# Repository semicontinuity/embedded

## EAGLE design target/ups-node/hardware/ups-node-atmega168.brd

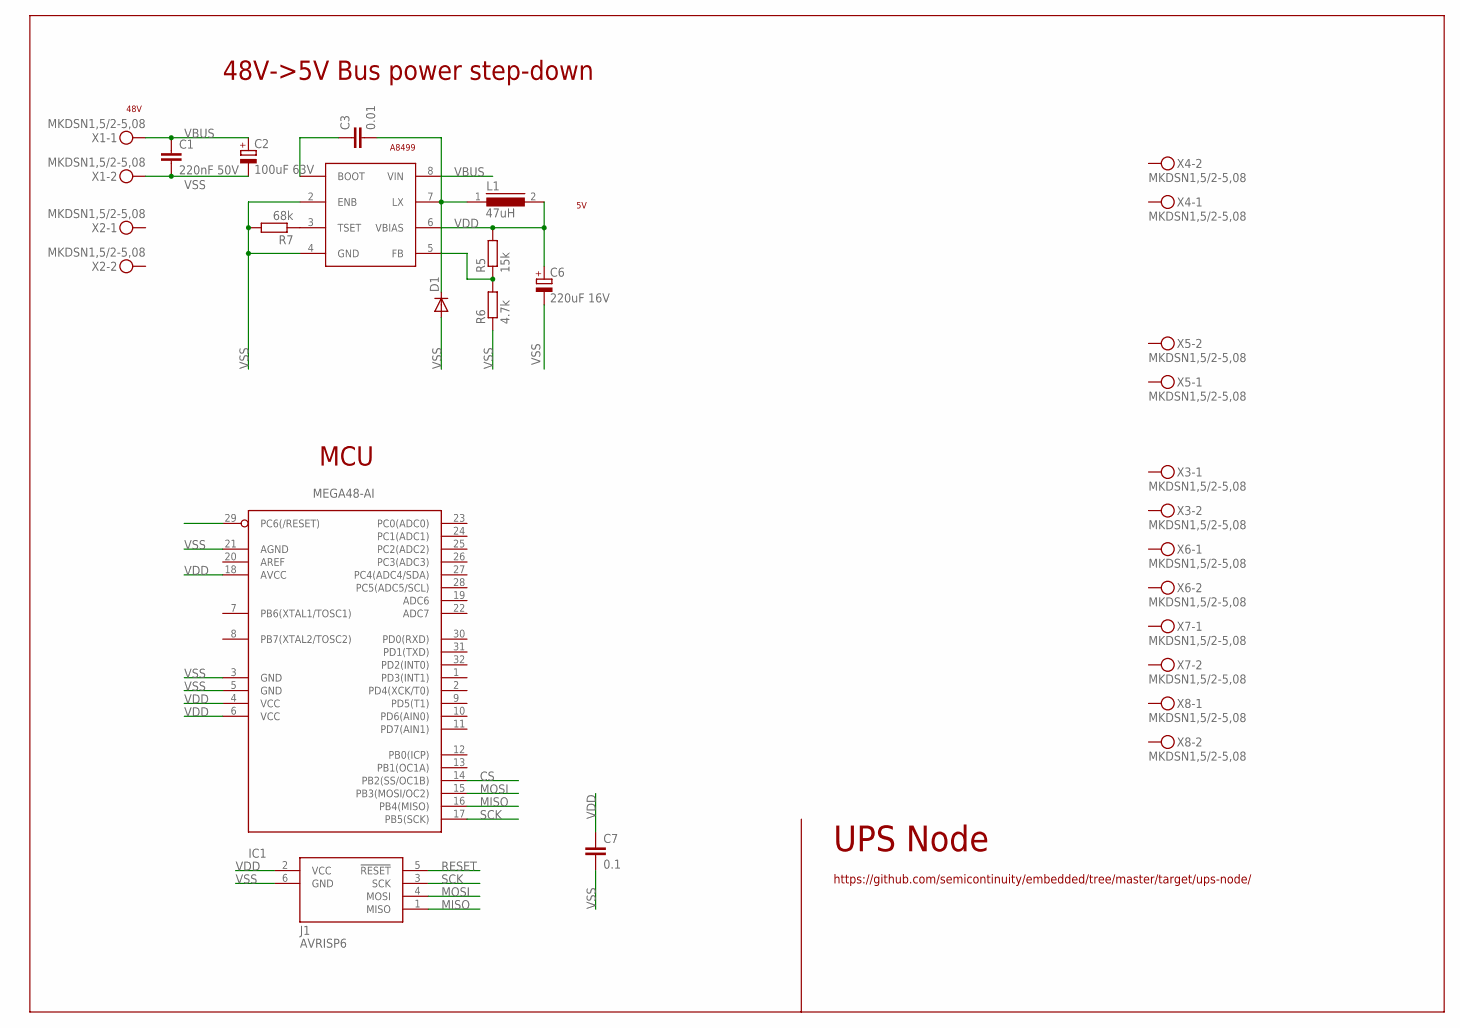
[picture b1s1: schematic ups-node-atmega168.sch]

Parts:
C1: 220nF 50V; C0805
C2: 100uF 63V; 153CLV-1010
C3: 0.01; C0805
C6: 220uF 16V; 153CLV-0605
C7: 0.1; C0805
D1: DIODE-SMB; SMB
IC1: MEGA48-AI; TQFP32-08
J1: AVRISP6; CON6P2R
L1: 47uH; DR127
R5: 15k; R0805
R6: 4.7k; R0805
R7: 68k; R0805
U$1: A8499; SO08
X1, X2, X3, X4, X5, X6, X7, X8: MKDSN1,5/2-5,08

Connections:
BOOT: C3.1, U$1.1 (BOOT)
CS: IC1.14 (PB2(SS/OC1B))
LX: C3.2, D1.C, L1.1, U$1.7 (LX)
MISO: IC1.16 (PB4(MISO)), J1.1 (MISO)
MOSI: IC1.15 (PB3(MOSI/OC2)), J1.4 (MOSI)
unnamed: R5.1, R6.2, U$1.5 (FB)
unnamed: R7.1, U$1.3 (TSET)
RESET: IC1.29 (PC6(/RESET)), J1.5 (!RESET)
SCK: IC1.17 (PB5(SCK)), J1.3 (SCK)
VBUS: C1.1, C2.+, U$1.8 (VIN), X1.1
VDD: C6.+, C7.1, IC1.4 (VCC), IC1.6 (VCC), IC1.18 (AVCC), J1.2 (VCC), L1.2, R5.2, U$1.6 (VBIAS)
VSS: C1.2, C2.-, C6.-, C7.2, D1.A, IC1.3 (GND), IC1.5 (GND), IC1.21 (AGND), J1.6 (GND), R6.1, R7.2, U$1.2 (ENB), U$1.4 (GND), X1.2

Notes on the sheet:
UPS Node
https://github.com/semicontinuity/embedded/tree/master/target/ups-node/
48V->5V Bus power step-down
MCU
A8499
48V

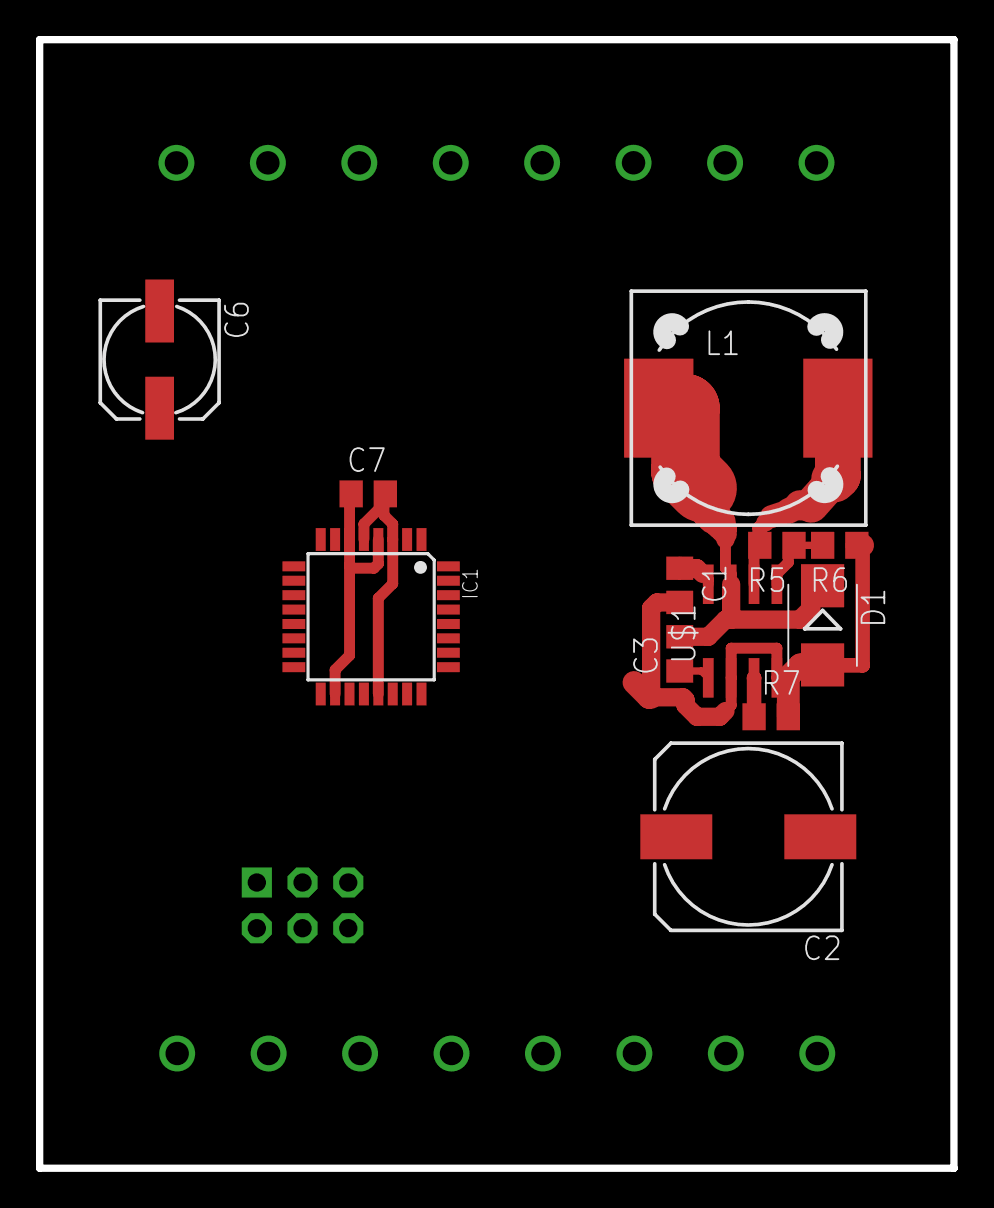
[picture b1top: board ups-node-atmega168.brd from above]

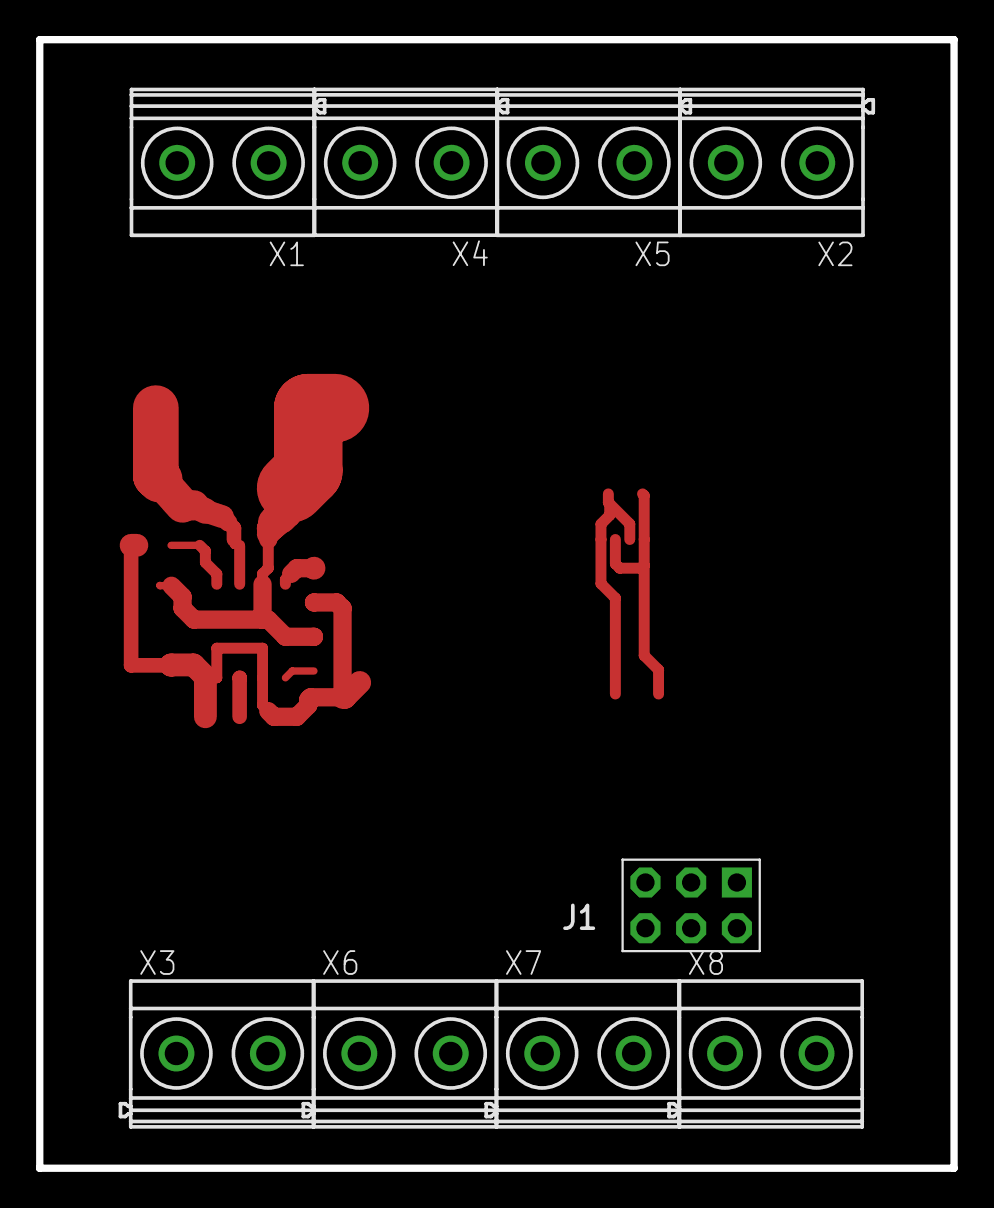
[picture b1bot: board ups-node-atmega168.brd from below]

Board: 2 copper layers, 50.8 x 62.7 mm, 21 parts (9 on the bottom side), 11 nets.

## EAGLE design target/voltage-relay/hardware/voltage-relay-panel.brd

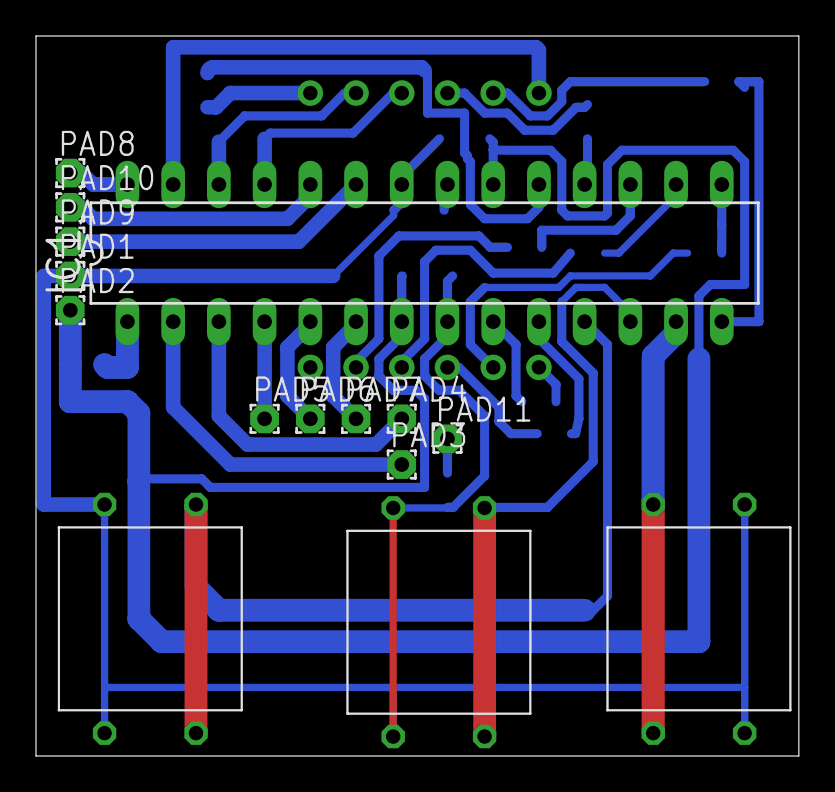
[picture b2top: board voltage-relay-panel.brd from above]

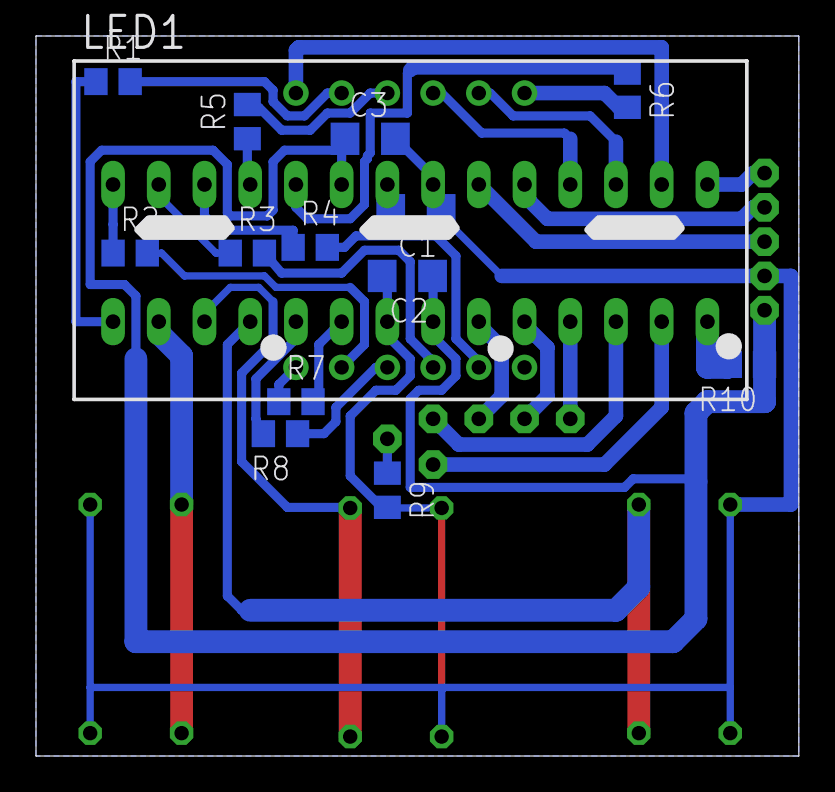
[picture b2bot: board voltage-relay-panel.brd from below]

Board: 2 copper layers, 42.4 x 40.0 mm, 29 parts (14 on the bottom side), 35 nets.

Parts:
C1, C2, C3: 0.1; C1206
IC1: MEGA8-P; DIL28-3
LED1: BA56-12YWA; BX56-12
PAD1, PAD2, PAD3, PAD4, PAD5, PAD6, PAD7, PAD8, PAD9, PAD10, PAD11: 1,6/0,8
R1, R2, R3, R4, R5, R6, R7, R8, R9: 470; R0805
R10: 10K; R0805
U$1, U$2, U$3: TL1105; LARGE

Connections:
B_MINUS: IC1.13, U$1.P$1, U$1.P$2
B_MODE: IC1.11, U$3.P$1, U$3.P$2
B_PLUS: IC1.12, U$2.P$1, U$2.P$2
DISP_A: LED1.11, R1.2
DISP_B: LED1.7, R6.2
DISP_C: LED1.4, R3.2
DISP_CA1: IC1.27, LED1.12
DISP_CA2: IC1.25, LED1.9
DISP_CA3: IC1.26, LED1.8
DISP_D: LED1.2, R2.2
DISP_DP: LED1.3, R8.1
DISP_E: LED1.1, R7.1
DISP_F: LED1.10, R5.2
DISP_G: LED1.5, R4.2
GND: C1.1, C2.2, C3.2, IC1.8, IC1.22, PAD1.1, R9.2, U$1.P$3, U$1.P$4, U$2.P$3, U$2.P$4, U$3.P$3, U$3.P$4
GPIO0: IC1.4, PAD5.1
GPIO1: IC1.5, PAD6.1
GPIO2: IC1.6, PAD7.1
GPIO3: IC1.23, PAD9.1
GPIO4: IC1.24, PAD10.1
GPIO5: IC1.28, PAD8.1
LED_G: IC1.3, PAD4.1
LED_R: IC1.2, PAD3.1
unnamed: IC1.1, R10.2
unnamed: PAD11.1, R9.1
unnamed: IC1.14, R1.1
unnamed: IC1.15, R2.1
unnamed: IC1.16, R3.1
unnamed: IC1.17, R4.1
unnamed: IC1.18, R5.1
unnamed: IC1.19, R6.1
unnamed: IC1.9, R7.2
unnamed: IC1.10, R8.2
unnamed: C1.2, IC1.21
VCC: C2.1, C3.1, IC1.7, IC1.20, PAD2.1, R10.1

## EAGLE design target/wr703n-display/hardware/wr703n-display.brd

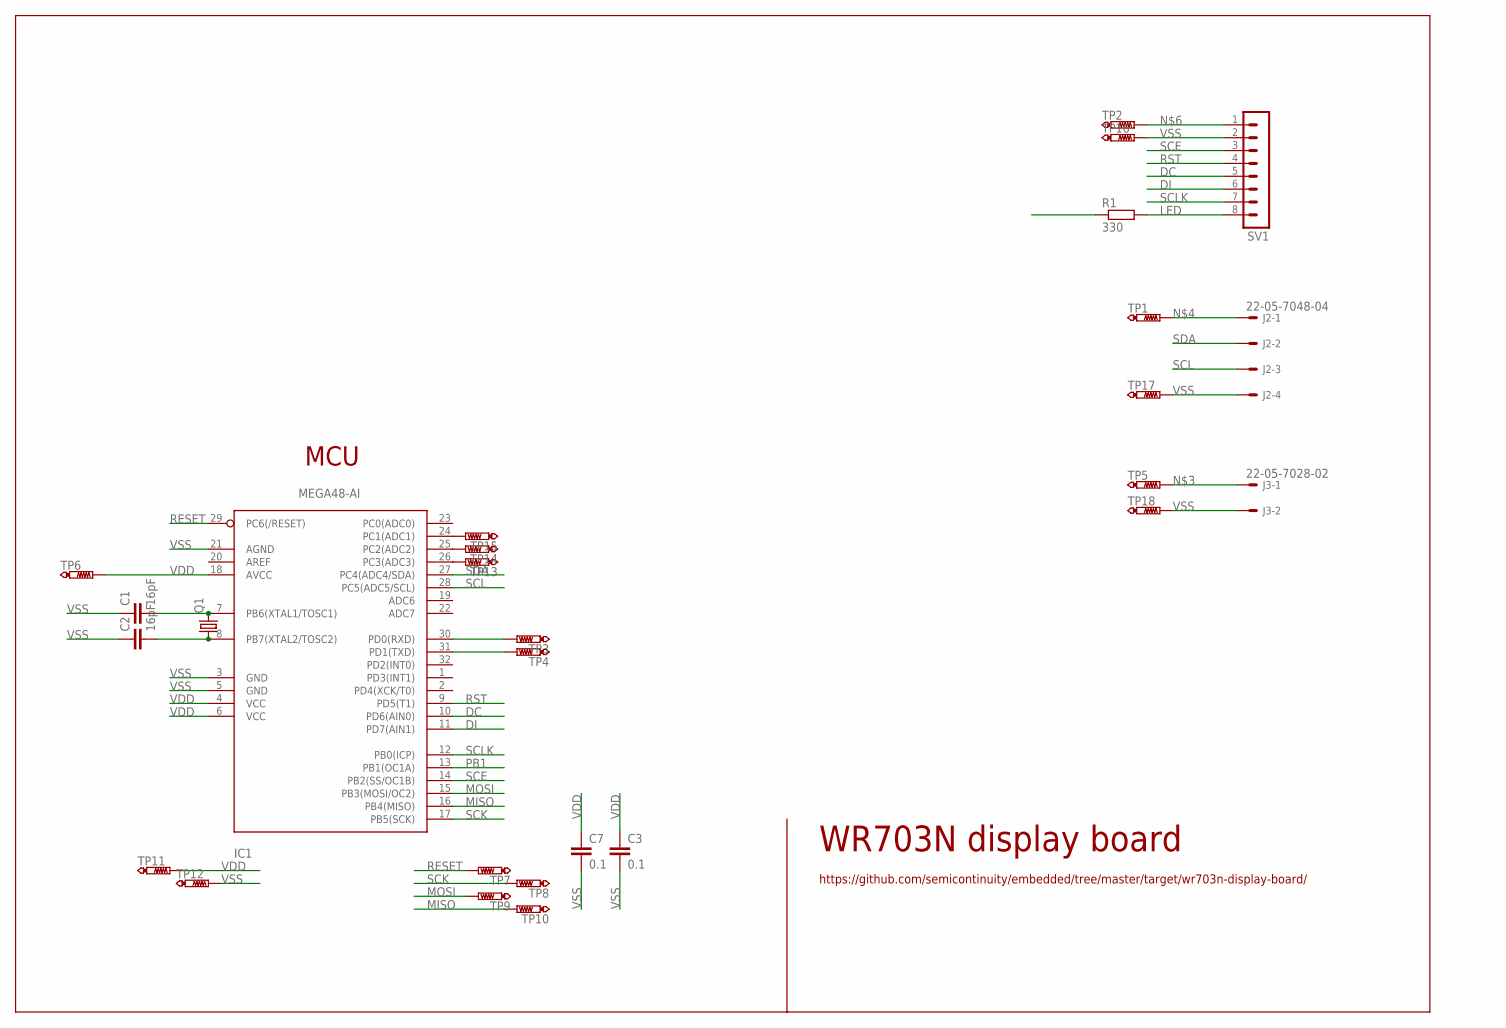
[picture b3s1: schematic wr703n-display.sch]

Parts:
C1, C2: 16pF; C0805
C3, C7: 0.1; C0805
IC1: MEGA48-AI; TQFP32-08
J2: 22-05-7048-04; 7395-04
J3: 22-05-7028-02; 7395-02
Q1: CRYSTALHC49S; HC49/S
R1: 330; R0805
SV1: MA08-1
TP1, TP2, TP3, TP4, TP5, TP6, TP16, TP17, TP18: PTR1B2,54; B2,54
TP7, TP8, TP9, TP10, TP11, TP12, TP13, TP14, TP15: PTR1TP17R; TP17R

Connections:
DC: IC1.10 (PD6(AIN0)), SV1.5
DI: IC1.11 (PD7(AIN1)), SV1.6
LED: R1.2, SV1.8
MISO: IC1.16 (PB4(MISO)), TP10.TP
MOSI: IC1.15 (PB3(MOSI/OC2)), TP9.TP
unnamed: C1.2, IC1.7 (PB6(XTAL1/TOSC1)), Q1.2
unnamed: C2.2, IC1.8 (PB7(XTAL2/TOSC2)), Q1.1
unnamed: J3.1, TP5.TP
unnamed: J2.1, TP1.TP
unnamed: IC1.31 (PD1(TXD)), TP4.TP
unnamed: SV1.1, TP2.TP
unnamed: IC1.26 (PC3(ADC3)), TP13.TP
unnamed: IC1.25 (PC2(ADC2)), TP14.TP
unnamed: IC1.24 (PC1(ADC1)), TP15.TP
PB1: IC1.13 (PB1(OC1A)), R1.1
RESET: IC1.29 (PC6(/RESET)), TP7.TP
RST: IC1.9 (PD5(T1)), SV1.4
RX: IC1.30 (PD0(RXD)), TP3.TP
SCE: IC1.14 (PB2(SS/OC1B)), SV1.3
SCK: IC1.17 (PB5(SCK)), TP8.TP
SCL: IC1.28 (PC5(ADC5/SCL)), J2.3
SCLK: IC1.12 (PB0(ICP)), SV1.7
SDA: IC1.27 (PC4(ADC4/SDA)), J2.2
VDD: C3.1, C7.1, IC1.4 (VCC), IC1.6 (VCC), IC1.18 (AVCC), TP6.TP, TP11.TP
VSS: C1.1, C2.1, C3.2, C7.2, IC1.3 (GND), IC1.5 (GND), IC1.21 (AGND), J2.4, J3.2, SV1.2, TP12.TP, TP16.TP, TP17.TP, TP18.TP

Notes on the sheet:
WR703N display board
https://github.com/semicontinuity/embedded/tree/master/target/wr703n-display-board/
MCU

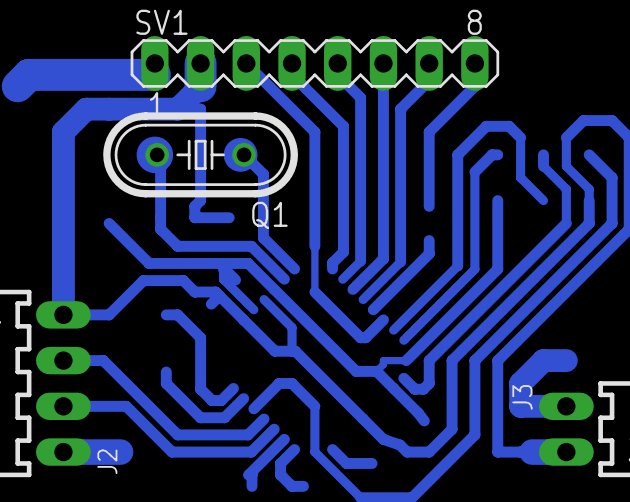
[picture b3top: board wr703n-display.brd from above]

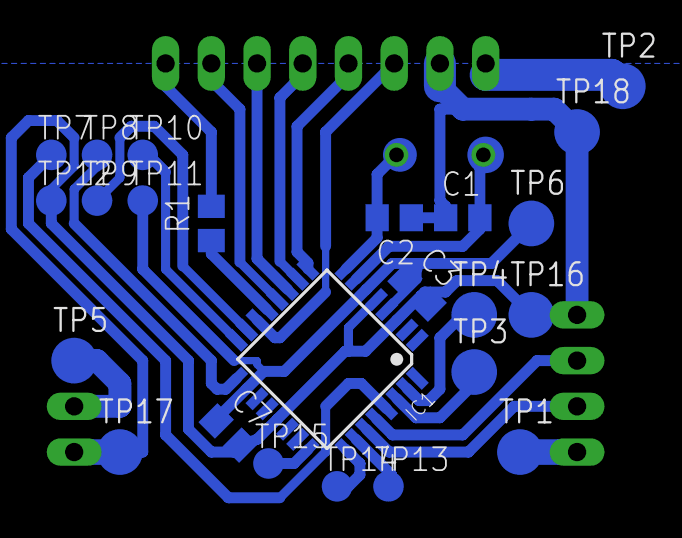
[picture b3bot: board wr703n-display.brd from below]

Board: 2 copper layers, 28 parts (24 on the bottom side), 25 nets.
